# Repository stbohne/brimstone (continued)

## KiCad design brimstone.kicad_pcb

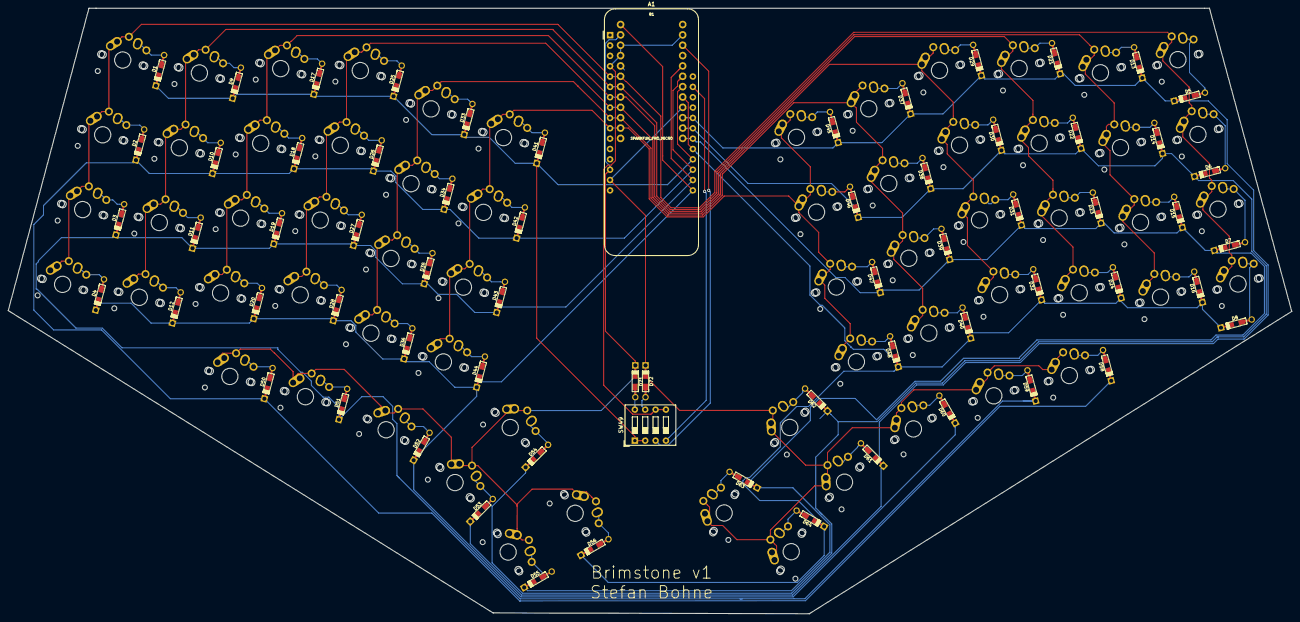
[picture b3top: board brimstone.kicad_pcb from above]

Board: 2 copper layers, 315.0 x 148.6 mm, 129 parts (0 on the bottom side), 83 nets.

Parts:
A1: Adafruit_Feather_32u4_BluefruitLE; Adafruit_Feather_32u4_FONA
B1: SPARKFUN_PRO_MICRO
D1, D2, D3, D4, D5, D6, D7, D8, D9, D10, D11, D12, D13, D14, D15, D16, D17, D18, D19, D20, D21, D22, D23, D24, D25, D26, D27, D28, D29, D30, D31, D32, D33, D34, D35, D36, D37, D38, D39, D40, D41, D42, D43, D44, D45, D46, D47, D48, D50, D51, D52, D53, D54, D55, D56, D58, D59, D60, D61, D62, D63, D64, D71, D72: D; Diode-dual
SW1, SW2, SW3, SW4, SW5, SW6, SW7, SW8, SW9, SW10, SW11, SW12, SW13, SW14, SW15, SW16, SW17, SW18, SW19, SW20, SW21, SW22, SW23, SW24, SW25, SW26, SW27, SW28, SW29, SW30, SW31, SW32, SW33, SW34, SW35, SW36, SW37, SW38, SW39, SW40, SW41, SW42, SW43, SW44, SW45, SW46, SW47, SW48, SW50, SW51, SW52, SW53, SW54, SW55, SW56, SW58, SW59, SW60, SW61, SW62, SW63, SW64: SW_Push; MX-Alps-Choc-1U-NoLED
SW49: SW_DIP_x04; SW_DIP_SPSTx04_Slide_9.78x12.34mm_W7.62mm_P2.54mm

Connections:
Col1: A1.5, B1.6, SW1.2, SW2.2, SW3.2, SW4.2, SW5.2, SW6.2, SW7.2, SW8.2
Col2: A1.6, B1.7, SW9.2, SW10.2, SW11.2, SW12.2, SW13.2, SW14.2, SW15.2, SW16.2
Col3: A1.7, B1.8, SW17.2, SW18.2, SW19.2, SW20.2, SW21.2, SW22.2, SW23.2, SW24.2
Col4: A1.8, B1.9, SW25.2, SW26.2, SW27.2, SW28.2, SW29.2, SW30.2, SW31.2, SW32.2
Col5: A1.9, B1.10, SW33.2, SW34.2, SW35.2, SW36.2, SW37.2, SW38.2, SW39.2, SW40.2
Col6: A1.10, B1.11, SW41.2, SW42.2, SW43.2, SW44.2, SW45.2, SW46.2, SW47.2, SW48.2
Col7: A1.14, B1.2, D71.1, SW50.2, SW51.2, SW52.2, SW53.2, SW54.2, SW55.2, SW56.2
Col8: A1.15, B1.16, D72.1, SW58.2, SW59.2, SW60.2, SW61.2, SW62.2, SW63.2, SW64.2
GND: A1.4, B1.3, B1.4, B1.23, SW49.5, SW49.6
unnamed: A1.27, SW49.4
unnamed: B1.22, SW49.3
unnamed: D1.2, SW1.1
unnamed: D2.2, SW2.1
unnamed: D3.2, SW3.1
unnamed: D4.2, SW4.1
unnamed: D5.2, SW5.1
unnamed: D6.2, SW6.1
unnamed: D7.2, SW7.1
unnamed: D8.2, SW8.1
unnamed: D9.2, SW9.1
unnamed: D10.2, SW10.1
unnamed: D11.2, SW11.1
unnamed: D12.2, SW12.1
unnamed: D13.2, SW13.1
unnamed: D14.2, SW14.1
unnamed: D15.2, SW15.1
unnamed: D16.2, SW16.1
unnamed: D17.2, SW17.1
unnamed: D18.2, SW18.1
unnamed: D19.2, SW19.1
unnamed: D20.2, SW20.1
unnamed: D21.2, SW21.1
unnamed: D22.2, SW22.1
unnamed: D23.2, SW23.1
unnamed: D24.2, SW24.1
unnamed: D25.2, SW25.1
unnamed: D26.2, SW26.1
unnamed: D27.2, SW27.1
unnamed: D28.2, SW28.1
unnamed: D29.2, SW29.1
unnamed: D30.2, SW30.1
unnamed: D31.2, SW31.1
unnamed: D32.2, SW32.1
unnamed: D33.2, SW33.1
unnamed: D34.2, SW34.1
unnamed: D35.2, SW35.1
unnamed: D36.2, SW36.1
unnamed: D37.2, SW37.1
unnamed: D38.2, SW38.1
unnamed: D39.2, SW39.1
unnamed: D40.2, SW40.1
unnamed: D41.2, SW41.1
unnamed: D42.2, SW42.1
unnamed: D43.2, SW43.1
unnamed: D44.2, SW44.1
unnamed: D45.2, SW45.1
unnamed: D46.2, SW46.1
unnamed: D47.2, SW47.1
unnamed: D48.2, SW48.1
unnamed: D50.2, SW50.1
unnamed: D51.2, SW51.1
unnamed: D52.2, SW52.1
unnamed: D53.2, SW53.1
unnamed: D54.2, SW54.1
unnamed: D55.2, SW55.1
unnamed: D56.2, SW56.1
unnamed: D58.2, SW58.1
unnamed: D59.2, SW59.1
unnamed: D60.2, SW60.1
unnamed: D61.2, SW61.1
unnamed: D62.2, SW62.1
unnamed: D63.2, SW63.1
unnamed: D64.2, SW64.1
unnamed: D71.2, SW49.8
unnamed: D72.2, SW49.7
Row1: A1.20, B1.18, D1.1, D9.1, D17.1, D25.1, D33.1, D41.1, SW49.1, SW49.2
Row2: A1.19, B1.19, D2.1, D10.1, D18.1, D26.1, D34.1, D42.1, D50.1, D58.1
Row3: A1.18, B1.20, D3.1, D11.1, D19.1, D27.1, D35.1, D43.1, D51.1, D59.1
Row4: A1.17, B1.1, D4.1, D12.1, D20.1, D28.1, D36.1, D44.1, D52.1, D60.1
Row5: A1.24, B1.15, D5.1, D13.1, D21.1, D29.1, D37.1, D45.1, D53.1, D61.1
Row6: A1.23, B1.14, D6.1, D14.1, D22.1, D30.1, D38.1, D46.1, D54.1, D62.1
Row7: A1.22, B1.13, D7.1, D15.1, D23.1, D31.1, D39.1, D47.1, D55.1, D63.1
Row8: A1.21, B1.17, D8.1, D16.1, D24.1, D32.1, D40.1, D48.1, D56.1, D64.1

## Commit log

2021-04-24 initial commit - Brimstone v1 ready for manufacturing
2022-05-23 added abandoned version of the 2nd Brimstone aka the ChopChop
2022-05-23 added final version of Brimstone 2 aka the ChopChop
